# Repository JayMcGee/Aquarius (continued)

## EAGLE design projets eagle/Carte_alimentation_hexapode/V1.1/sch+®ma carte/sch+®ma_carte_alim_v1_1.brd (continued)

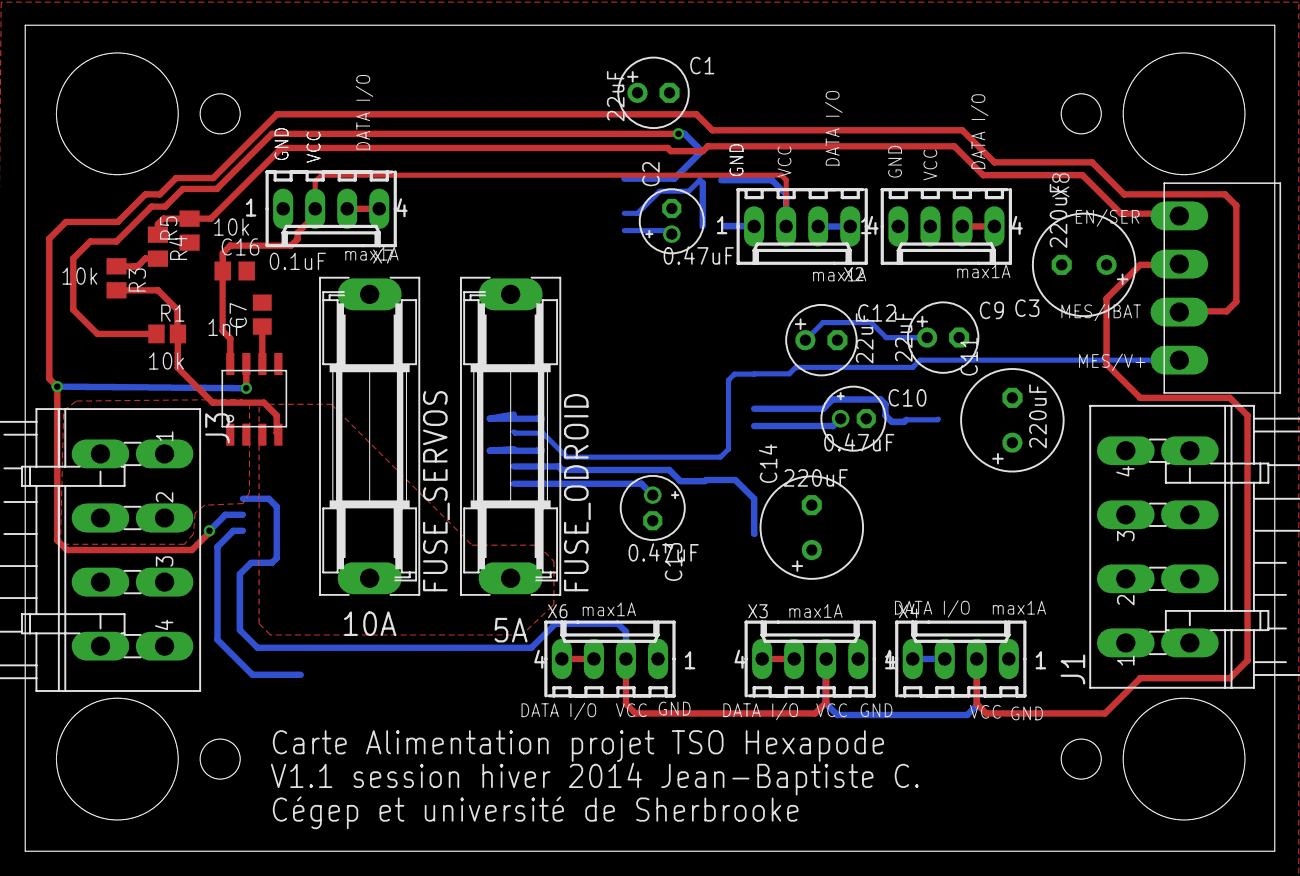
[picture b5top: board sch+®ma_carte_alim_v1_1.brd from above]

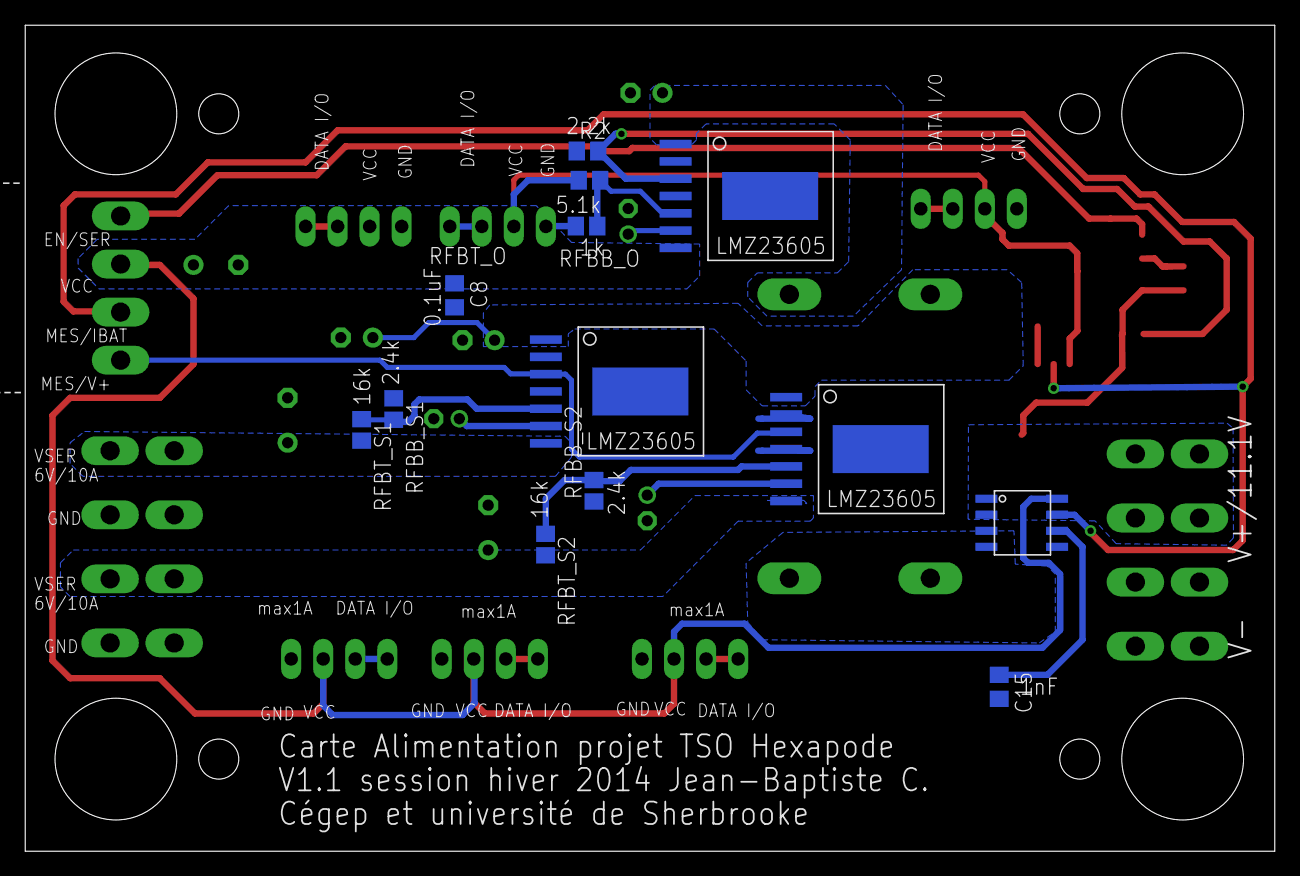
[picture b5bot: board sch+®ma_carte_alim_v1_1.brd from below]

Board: 2 copper layers, 99.1 x 65.5 mm, 40 parts (13 on the bottom side), 27 nets.

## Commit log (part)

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2000-01-01 First version of configuration page on web server
2015-01-19 Correction et modification de certaines phrases
2015-01-19 Added folder src/build_src to contain main project source code, mainly drivers but also the main service
2015-01-19 Added src/test_src to contain all unit tests that were produced during the project
2015-01-19 Simple script to be updated that copies the new web page to its location in /var/www
2015-01-19 Example .json message to the aquarius database
2015-01-21 Modification du code de communication I2C
    Permets de tester la communication et d'envoyer des commandes en
    utilisant la ligne de commande
2015-01-21 Adaptation du script pour l'emplacement relatif
2015-01-22 Added tclap
    Added tclap library to include folder. Will be used to manage command
    line arguments
2015-01-22 Deleted unused SuperEasyJSON library
2015-01-22 Added SuperEasyJSON library to include directory
2015-01-22 Updated I2C test Makefile to follow modifications
    Follows the new library locations to blacklib
2015-01-23 Schematic updated with new PCB
    Done by JayMcGee
2015-01-24 Updated WebSite,
    Added Calibrate buttons and display scripts
2015-01-24 Script to enable internet over USB
    Useful to temporarly put the BeagleBone in a USB sourced internet mode,
    when no other source is available
2015-01-26 Added a switch to select mode of operation
2015-02-04 Updated schematic
    Added:
    RTC
    Logic for power management
2015-02-07 Synchronisation des fichiers
    Yay! So much data
2015-02-08 Ajout des fichiers manquants dans le dossier node-bootstrap
2015-02-08 Ajout de dossier dans node_modules
2015-02-09 Modified Website, fixed error where charts would updates on empty data values, In app.js replace de data of the sensor for a random number generator for test purpose
2015-02-11 First draft of driver communications
2015-02-13 Modification au makefile du DHT22 et autre modifs
    Sur le board
2015-02-13 Premier brouillons des pilotes pour deux capteurs
    Température et humidité interne ainsi que le capteur de température
    externe
2015-02-13 Modified Index.html and style.css to fit the interface to a wider variety of display
2015-02-14 Created new folder to avoid overwrite of brd modifications
2015-02-14 Comments and optimization on OneWire reader
    Added some new defines in OneWireDevice and comments to the main
    executable
2015-02-14 Continued work on PH driver
    Added zone for all command except transfer to serial mode. Added a lot
    of defines to aid in coding. Simplified the command identification,
    refactored some variables to some more expletive names
2015-02-16 PCB update
    Changed connectors for battery input
2015-02-18 PCB Update and modified name of Atlas driver cpp's
2015-02-19 PCB JayMcGee Version
2015-02-19 Added a new PCB version to be selected or not
2015-02-19 Updated I2C pH driver to latest version
2015-02-20 Finalised Atlas pH driver for testing
2015-02-20 Mise a jour du PCB version Jay_brd pour finalisation
2015-02-23 Finalisation du pcb avant le test 4pcb
2015-02-23 Final modifications to PCB for production
2015-02-23 Updated App.js and Index.js
2015-02-26 Synchronisation du code et du board
2015-02-26 Added K and DO driver first pass
2015-02-27 Compilation correction on new commun file
    Added build details to other drivers so that de commun can compile. This
    will need to change to only compile that file once
    I2C DO an K driver corrections and modifications on I2C general driver
    to read adequatly temperature compensation data
2015-02-27 first draft of RTC functions
2015-02-27 Synchro
2015-02-28 Completed DO driver to output good data
    And modified the string split length verification method to use the
    DATA_QTY constant
2015-03-01 Ajout d'un fichier avec un insert dans la base de données
2015-03-01 Refactored some details and corrected errors on install script
2015-03-01 Added Scheduler,
2015-03-09 After spring break synchronisation
2015-03-09 First draft of NodeJS function for db access and processing
2015-03-13 RTC code in pyhton added
    Version 1, python was more efficient and faster to code than C++ and
    Blacklib was not cooperating
2015-03-13 RTC code updated to latest version, almoste finished
2015-03-16 Mise a jour des pilotes du RTC et de APP.js fonctionnel
2015-03-18 Removed old node package, Created a service to start server on boot and added execSync to app.js
2015-03-18 Added a date-time picker to the form.html configuration page
2015-03-18 Added the configuration page and started the backend logic to support it
2015-03-18 Add service file
2015-03-18 Updated form
2015-03-18 follow up
2015-03-18 Deleted deprecated tty.js
2015-03-18 Added new database export, with base data inputted
2015-03-18 Moved NodeJS database files to db folder
2015-03-18 Added first draft of mySql configuration read
2015-03-18 Corrected app path temporarly to accomodate the database read not implemented
2015-03-18 Added new configuration set and get to aquariusSensorHelper
2015-03-18 Added first pass of mode selection following switch on board
2015-03-18 Second draft of sync read + async insert into final database. app.js now retrieves installed sensor list from database
2015-03-20 Splitted the javascript into files, see node-bootstrap/public/scripts
2015-03-20 Fixed Form.html js
2015-03-20 AquariusConfig implemented sendConfig
2015-03-20 Added exec folder with content and backup of SQL database with Description field in config table
2015-03-20 Retry on commit before
2015-03-20 Adds functional configuration page to project, can now configure some parameters from /form.html Service also keeps track of last know date
2015-03-20 Updated APP.js to send config data to form.html and updated name of attempts to ATTEMPT_RETIES
2015-03-21 Added more messages in install.sh process Comments and optimization in app.js Created a configuration var for current operative mode
2015-03-23 Added new examples of SIM908 communication, succesful tests with good communications
2015-03-23 Added some buttons to the interface to change modes
2015-03-25 Updated Database queries to new refactored table names
2015-03-25 Added a new backup of data in db
2015-03-25 Remodified sql backup with a renaming
2015-03-27 Added log file creation
    le ruivo
2015-03-27 Merged version of app.js
2015-03-27 Finalize Json formatter
2015-03-27 Git sync with new SQL query for DATA to send to JSON
2015-03-27 Added latest backup of data
2015-03-27 Added connection to pubNub
2015-03-27 Added additional data for data query
2015-03-27 Prepared for test
2015-03-30 Added synchrounous watchdog execution
2015-03-30 Added retry on execution , corrected watchdog as a sync exec
2015-04-08 Added new code to prepare JSON send tests to ClouDIA Added to install script the disable hdmi cape part that was missing
2015-04-08 Added LED flash or stay on depending on operation mode
2015-04-08 Added error management to OneWire driver. Changed logic of DEL python driver to match desired functionality
2015-04-10 Added Start and stop to SIM908 for GPS module
2015-04-10 Corrected bug that stopped reading sensors. Was caused by DEL functions take to much CPU time. Put as async exec
2015-04-10 Adafruit I2C added to install
2015-04-12 Added 1W DTS file and minor additions to SIM908 driver
    Install SH to be completed with added compilation of DTS of 1W driver.
2015-04-13 Fixed retry test in app.js on sensor reading
2015-04-13 Readded ADC.py for battery voltage reading
2015-04-13 Added latest SQL export
2015-04-13 Sync with newest web files
2015-04-13 Added new git ignored files, log and nulllog
2015-04-15 Fixed syntax error in index.html
2015-04-15 Implemented the update of CircleStats
2015-04-17 Sync with branch
2015-04-17 Deleted surplus, added config usage of send address
2015-04-17 Added rc.local to installation. Added app.js config bit to select auto mode functionnality (reboot or not)
2015-04-17 Started implementing calibration interface
2015-04-18 Small error on command line to close all power
2015-04-20 Cloudia serveur communication fixed
2015-04-20 Added new version of database
2015-04-22 Added SIM908 settings
2015-04-22 Interfaces tweaks
2015-04-27 Uptaded the script to calibrate the sensors
2015-04-27 Minor corrections to GPS driver in preparation to integration
2015-04-29 Corrected errors in calibration of K stamp, does a dry calibration with a clear
2015-04-29 Inverted DO output
2015-05-02 Added new functions to SIM908 driver and test files
2015-05-02 Changed Interfaces
2015-05-02 Charts
2015-05-02 Modification à la page web
2015-05-02 Started comments on driver files and some images for documentation purposes
2015-05-04 Added new date update function and deactivated RTC in auto no reboot mode
2015-05-04 Correct merge errors
2015-05-05 Cleanup of some includes, changed fona and gprs copy into make of sim908 driver Changed install.sh orders and added make Moved install of 1W driver dts into make
2015-05-06 Corrected driver Atlas to use a argument passed temperature compensation
2015-05-06 Corrected DEL execution recall and sequencing
2015-05-06 Added real good database export
2015-05-08 Update to add precision on read value
2015-05-08 Minor corrections for milestone 1
2015-05-08 Modified app to use new precision values
2015-05-08 Corrected error in index.html that was not sending emits to server
2015-05-08 Modified install.sh to use latest db backup and install phpmyadmin
2015-05-08 Final commit before test
2015-05-08 Getting bealge1 up to date
2015-05-08 Corrected for real the presence of a non existant SQL column
2015-05-08 New database export
2015-05-08 Added TIM gprs files, with password to be added
2015-05-08 Added check for enabled sensor
2015-05-09 Added echo to apache2.conf tu use phpmyadmin
2015-05-09 Removed t_Physical.cloudia_id as was unused. Changed in app.js also to keep functionality
2015-05-09 Completed C++ comments
2015-05-09 Finished comment on switches, adc and LED gpio files Renamed LED gpio files to better explain their use Changed names for LED files in app.js
2015-05-10 Added Comments and Doc to Aquarius_Calibrate.js
2015-05-10 Added comments to SIM908 driver
2015-05-10 Finished comments in RTC driver file
2015-05-10 Added Aquarius_Map.js and Aquarius_UITools.js
2015-05-10 Renamed aquariusSensorHelper to more friendly and descriptive name Commented code in app.js and refactored function and var names Added new file to be used as script to disable USR LED in auto mode
2015-05-10 UI tweaks
2015-05-10 Deleted unecessary files
2015-05-11 Corrected calibration logic in index.html to send value
2015-05-11 Removed debug string in PH driver
2015-05-12 Comments and refactoring, removed some unused vars
2015-05-13 Finished comments in app.js
2015-05-13 Finished comments in toolkit
2015-05-14 Added comments to index.html
2015-05-14 Changed sql file to use latest
2015-05-16 Updated SIM908 files and service to work with new parameters
2015-05-16 Added new Installation sequence to set K sensor as 0.1 constant
2015-05-16 Addde internet script over USB
2015-05-28 Removed unused watchdog files
2015-05-28 Added sensor unit to configuration page
2015-05-28 Added K configuration on first install
2015-05-28 Modified to enable a virtual click on the link towards the exported file
2015-05-29 Testing calibration confirmation
2015-05-29 Corrected duplicate emit designation
2015-05-29 Removed turning arrow on sensor arrow
2015-05-29 Added all missing configuration parameters to form.html
2015-05-29 Missing two double points after condition checking
2015-05-29 Added array lenght checking in data output
2015-05-29 Corrected error on form, debug level would modifiy the html and not .val()
2015-05-29 Preliminary database export functions
2015-05-30 Added a new one point calibration to index.html
2015-06-01 Added emit managaement for One point calibration
2015-06-01 Removed debug string completely and readded the good ones
2015-06-01 Changed output of debug strings
2015-06-02 Update 2
2015-06-02 Added debug to checkifFix
2015-06-02 Added functions to automaticly change the DS18B20 address. To be tested
2015-06-02 Added functions to stop LED on the pcb during execution of auto mode
2015-06-03 Added functions to manage data plan and created a function to send all unsent data to cloudia
2015-06-04 Final backup of database before deployement
2015-06-08 Added function to send all data through internet connection in manual mode
2015-06-08 Changed Database import file to latest version
2015-06-08 Added managing the date update in configuration page
2015-06-08 Added Charts to Results
